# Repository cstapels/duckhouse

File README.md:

# duckhouse
controller for the duck house

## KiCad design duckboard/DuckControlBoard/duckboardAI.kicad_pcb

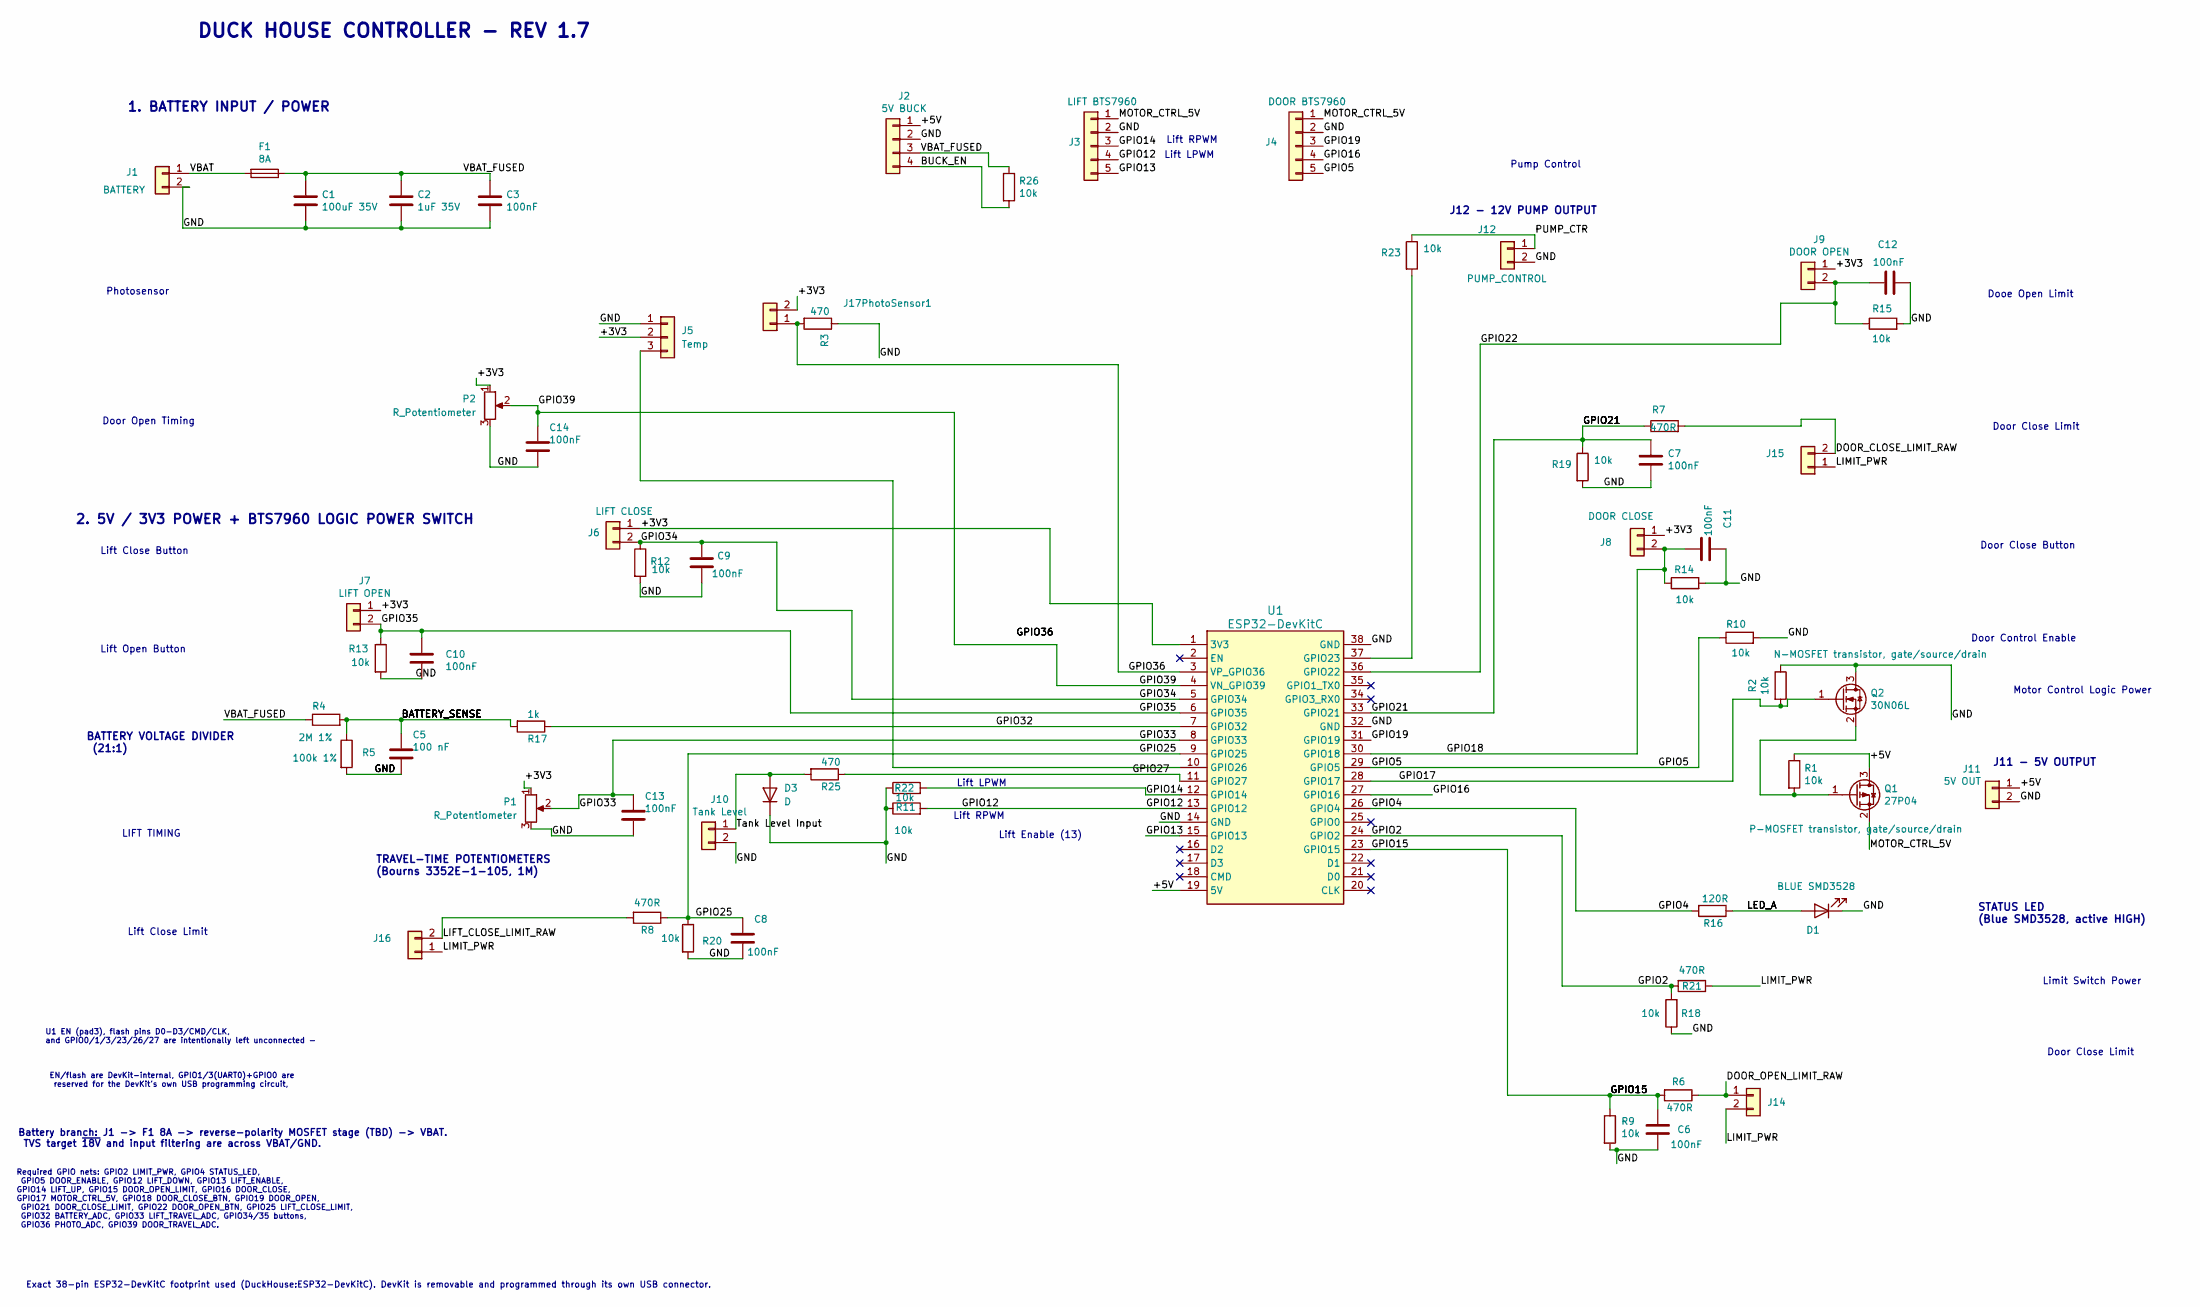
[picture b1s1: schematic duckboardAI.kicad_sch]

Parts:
C1: 100uF 35V; C_0805_2012Metric
C2: 1uF 35V; C_0805_2012Metric
C3, C6, C7, C8, C9, C10, C11, C12, C13, C14: 100nF; C_0805_2012Metric
C5: 100 nF; C_0805_2012Metric
D1: BLUE SMD3528; LED_Everlight-SMD3528_3.5x2.8mm_67-21ST
D3: D; D_0805_2012Metric
F1: 8A; Fuseholder_Cylinder-5x20mm_Schurter_0031_8201_Horizontal_Op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
J1: BATTERY; TerminalBlock_MaiXu_MX126-5.0-02P_1x02_P5.00mm
J2: 5V BUCK; PinHeader_1x04_P2.54mm_Vertical
J3: LIFT BTS7960; JST_EH_B5B-EH-A_1x05_P2.50mm_Vertical
J4: DOOR BTS7960; JST_EH_B5B-EH-A_1x05_P2.50mm_Vertical
J5: Temp; JST_EH_B3B-EH-A_1x03_P2.50mm_Vertical
J6: LIFT CLOSE; JST_EH_S2B-EH_1x02_P2.50mm_Horizontal
J7: LIFT OPEN; JST_EH_S2B-EH_1x02_P2.50mm_Horizontal
J8: DOOR CLOSE; JST_EH_S2B-EH_1x02_P2.50mm_Horizontal
J9: DOOR OPEN; JST_EH_S2B-EH_1x02_P2.50mm_Horizontal
J10: Tank Level; JST_EH_S2B-EH_1x02_P2.50mm_Horizontal
J11: 5V OUT; JST_EH_S2B-EH_1x02_P2.50mm_Horizontal
J12: PUMP_CONTROL; TerminalBlock_MaiXu_MX126-5.0-02P_1x02_P5.00mm
J14: DOOR_OPEN_LIMIT; JST_EH_S2B-EH_1x02_P2.50mm_Horizontal
J15: DOOR_CLOSE_LIMIT; JST_EH_S2B-EH_1x02_P2.50mm_Horizontal
J16: LIFT_CLOSE_LIMIT; JST_EH_S2B-EH_1x02_P2.50mm_Horizontal
J17PhotoSensor1: Conn_01x02; TerminalBlock_MaiXu_MX126-5.0-02P_1x02_P5.00mm
P1, P2: R_Potentiometer; Potentiometer_Piher_T-16L_Single_Vertical_Hole
Q1: 27P04; TO-220-3_Horizontal_TabUp
Q2: 30N06L; TO-220-3_Horizontal_TabUp
R1, R2, R9, R10, R11, R12, R13, R14, R15, R18, R19, R20, R22, R23, R26: 10k; R_0603_1608Metric
R3, R25: 470; R_0603_1608Metric
R4: 2M 1%; R_0603_1608Metric
R5: 100k 1%; R_0603_1608Metric
R6, R7, R8, R21: 470R; R_0603_1608Metric
R16: 120R; R_0603_1608Metric
R17: 1k; R_0603_1608Metric
U1: ESP32-DevKitC

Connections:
/+3V3: J5.2, J6.1, J7.1, J8.1, J9.1, J17PhotoSensor1.2, P1.1, P2.1, U1.1 (3V3)
/+5V: J2.1, J11.1, Q1.3 (D), R1.1, U1.19 (5V)
/BATTERY_SENSE: C5.1, R4.2, R5.1, R17.2
/BUCK_EN: J2.4, R26.2
/DOOR_CLOSE_LIMIT_RAW: J15.2, R7.2
/DOOR_OPEN_LIMIT_RAW: J14.1, R6.1
/GND: C1.2, C2.2, C3.2, C5.2, C6.2, C7.2, C8.2, C9.2, C10.2, C11.1, C12.2, C13.2, C14.2, D1.1 (K), D3.1 (K), J1.2, J2.2, J3.2, J4.2, J5.1, J10.2, J11.2, J12.2, P1.3, P2.3, Q2.3 (D), R2.1, R3.1, R5.2, R9.2, R10.2, R11.1, R12.2, R13.2, R14.2, R15.2, R18.1, R19.2, R20.2, R22.1, U1.14 (GND), U1.32 (GND), U1.38 (GND)
/GPIO2: R18.2, R21.2, U1.24 (GPIO2)
/GPIO4: R16.2, U1.26 (GPIO4)
/GPIO5: J4.5, R10.1, U1.29 (GPIO5)
/GPIO12: J3.4, R11.2, U1.13 (GPIO12)
/GPIO13: J3.5, U1.15 (GPIO13)
/GPIO14: J3.3, R22.2, U1.12 (GPIO14)
/GPIO15: C6.1, R6.2, R9.1, U1.23 (GPIO15)
/GPIO16: J4.4, U1.27 (GPIO16)
/GPIO17: Q2.1 (G), R2.2, U1.28 (GPIO17)
/GPIO18: C11.2, J8.2, R14.1, U1.30 (GPIO18)
/GPIO19: J4.3, U1.31 (GPIO19)
/GPIO21: C7.1, R7.1, R19.1, U1.33 (GPIO21)
/GPIO22: C12.1, J9.2, R15.1, U1.36 (GPIO22)
/GPIO25: C8.1, R8.1, R20.1, U1.9 (GPIO25)
/GPIO27: R25.1, U1.11 (GPIO27)
/GPIO32: R17.1, U1.7 (GPIO32)
/GPIO33: C13.1, P1.2, U1.8 (GPIO33)
/GPIO34: C9.1, J6.2, R12.1, U1.5 (GPIO34)
/GPIO35: C10.1, J7.2, R13.1, U1.6 (GPIO35)
/GPIO36: J17PhotoSensor1.1, R3.2, U1.3 (VP_GPIO36)
/GPIO39: C14.1, P2.2, U1.4 (VN_GPIO39)
/LED_A: D1.2 (A), R16.1
/LIFT_CLOSE_LIMIT_RAW: J16.2, R8.2
/LIMIT_PWR: J14.2, J15.1, J16.1, R21.1
/MOTOR_CTRL_5V: J3.1, J4.1, Q1.2 (S)
/PUMP_CTR: J12.1, R23.1
/Tank Level Input: D3.2 (A), J10.1, R25.2
/VBAT: F1.2, J1.1
/VBAT_FUSED: C1.1, C2.1, C3.1, F1.1, J2.3, R4.1, R26.1
unnamed: J5.3, U1.10 (GPIO26)
unnamed: Q1.1 (G), Q2.2 (S), R1.2
unnamed: R23.2, U1.37 (GPIO23)

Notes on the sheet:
Lift Open Button
BATTERY VOLTAGE DIVIDER (21:1)
Lift RPWM
Lift LPWM
DUCK HOUSE CONTROLLER - REV 1.7
J11 - 5V OUTPUT
Door Close Limit
TRAVEL-TIME POTENTIOMETERS (Bourns 3352E-1-105, 1M)
Lift Close Button
Battery branch: J1 -> F1 8A -> reverse-polarity MOSFET stage (TBD) -> VBAT. TVS target ~{18V} and input filtering are across VBAT/GND.
EN/flash are DevKit-internal, GPIO1/3(UART0)+GPIO0 are reserved for the DevKit's own USB programming circuit,
1. BATTERY INPUT / POWER
STATUS LED (Blue SMD3528, active HIGH)
LIFT TIMING
Motor Control Logic Power
Door Control Enable
Lift Enable (13)
J12 - 12V PUMP OUTPUT
2. 5V / 3V3 POWER + BTS7960 LOGIC POWER SWITCH
Door Close Button
Limit Switch Power
Exact 38-pin ESP32-DevKitC footprint used (DuckHouse:ESP32-DevKitC). DevKit is removable and programmed through its own USB connector.
Pump Control
Door Open Timing
Lift Close Limit
Required GPIO nets: GPIO2 LIMIT_PWR, GPIO4 STATUS_LED, GPIO5 DOOR_ENABLE, GPIO12 LIFT_DOWN, GPIO13 LIFT_ENABLE, GPIO14 LIFT_UP, GPIO15 DOOR_OPEN_LIMIT, GPIO16 DOOR_CLOSE, GPIO17 MOTOR_CTRL_5V, GPIO18 DOOR_CLOSE_BTN, GPIO19 DOOR_OPEN, GPIO21 DOOR_CLOSE_LIMIT, GPIO22 DOOR_OPEN_BTN, GPIO25 LIFT_CLOSE_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
U1 EN (pad3), flash pins D0-D3/CMD/CLK, and GPIO0/1/3/23/26/27 are intentionally left unconnected -
Dooe Open Limit
Photosensor

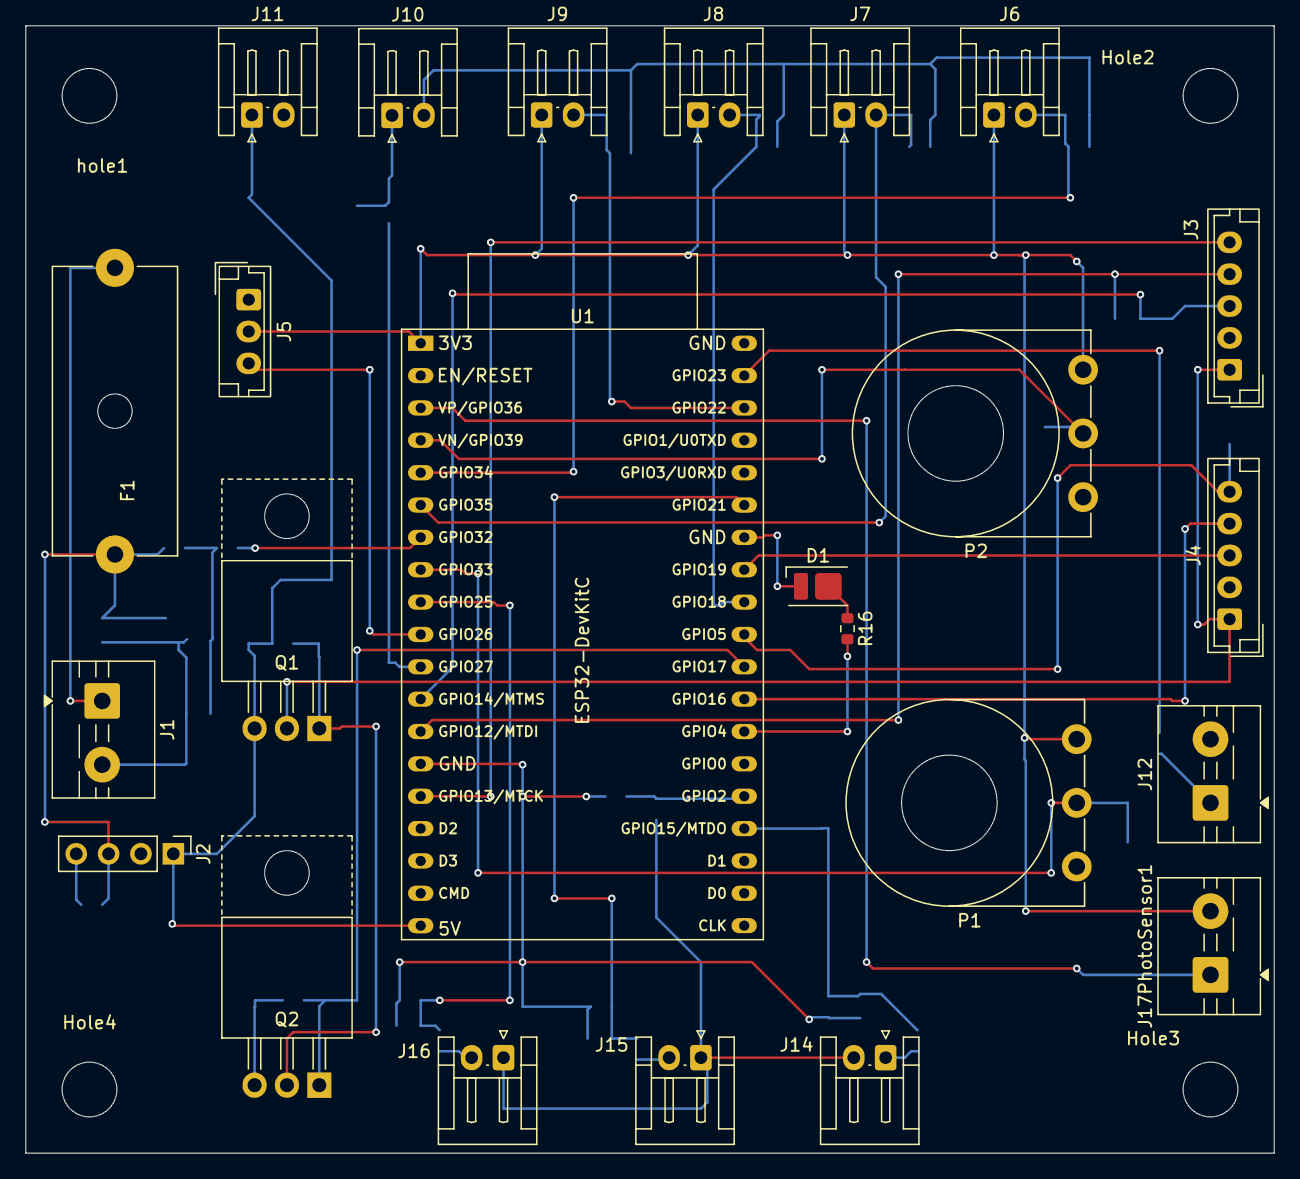
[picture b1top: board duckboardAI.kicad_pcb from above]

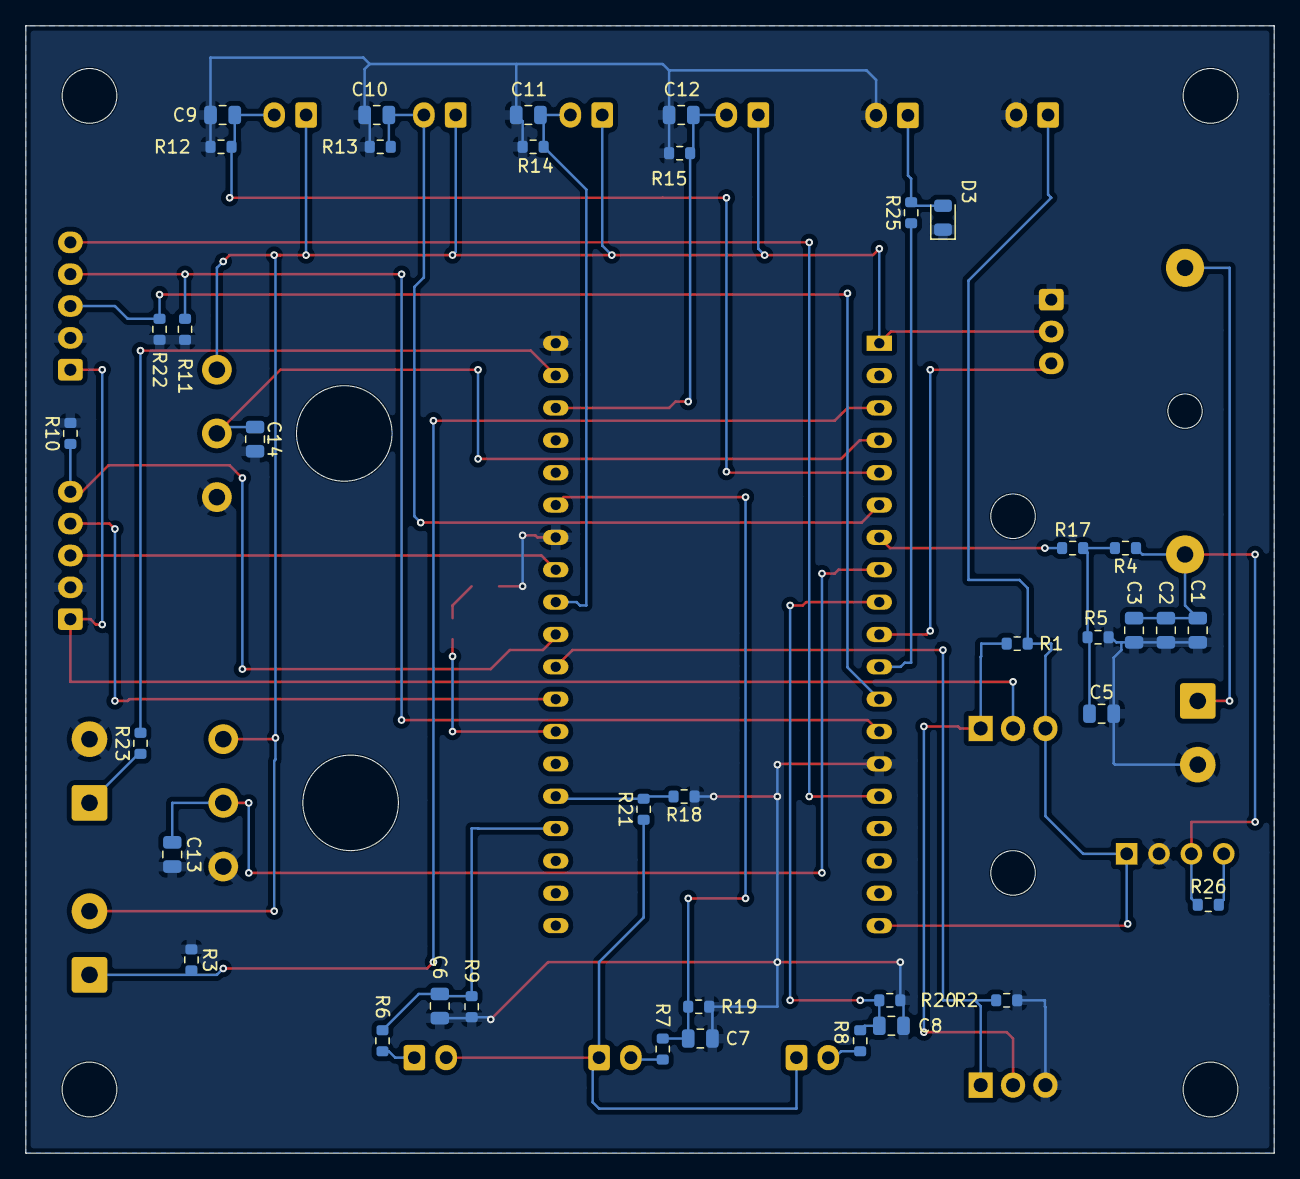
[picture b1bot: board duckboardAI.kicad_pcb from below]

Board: 2 copper layers, 98.0 x 88.5 mm, 66 parts (38 on the bottom side), 39 nets.

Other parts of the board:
Hole2, Hole3, Hole4: MountingHole_4.3mm_M4
hole1: MountingHole_4.3mm_M4

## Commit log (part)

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2023-05-15 where is this going to go
2023-05-15 first commit, added 2 for open lift
2024-02-18 long press, working light other large improvements
2024-12-14 add temperature measurement routine
2024-12-15 deploy changes and init correct
2025-02-17 temp?
2025-04-10 Measure two dht sensors in the garage for baby ducks
    title says it all
2025-04-10 a few updates
    restart on too many connect attempts, move the delay up
2025-11-20 update connection
    growing delay time plus reset after 9
2025-11-30 changed try counter
    seems like the cable was bad
2025-12-15 updated page with divs and more duckplots
2025-12-20 simplification but wrong number for open
2025-12-20 larger buttons for mobile, fix missign iframes,
2025-12-20 include battery plot
